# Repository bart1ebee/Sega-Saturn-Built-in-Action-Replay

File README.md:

# Sega-Saturn-Built-in-Action-Replay

This will allow you to take an action replay for a Sega Saturn and solder it to the under side of the cart connector to bypass a bad slot.

This currently is setup to work with VA 0 and .5 motherboards I believe it will work with VA1 but do not have a system to test with. In the future I'd like to make the same board or possibly a few boards for all revisions.

## Features

- Enable / Disable with a switch
- Swap between Action Replay and [Pseudo Saturn Kai](https://ppcenter.webou.net/pskai/)
- If PAL equations can be extracted this could be buildable without buying an action replay 

## Parts Needed

- PCB
- Action Replay containing the following
    - 2x HM5117800J
    - 2x sst29ee020-120-4c-nh
    - 2x 74157
    - PAL16L8 
    - PAL24
- Soldering skills
- Optional: the STL folder has a fake cart slot with catches to hold the Action Replay Cart that I added switches to.

## Building

1. Order Boards from a PCB supplier
2. Disassemble an Action replay and assemble on new board
3. SW1 is a SPDT On-On switch and SW2 is a SPST switch On-Off
4. Solder to underside of card slot

## Help Wanted

 Anyone that can extract the logic equations from the PAL Chips.

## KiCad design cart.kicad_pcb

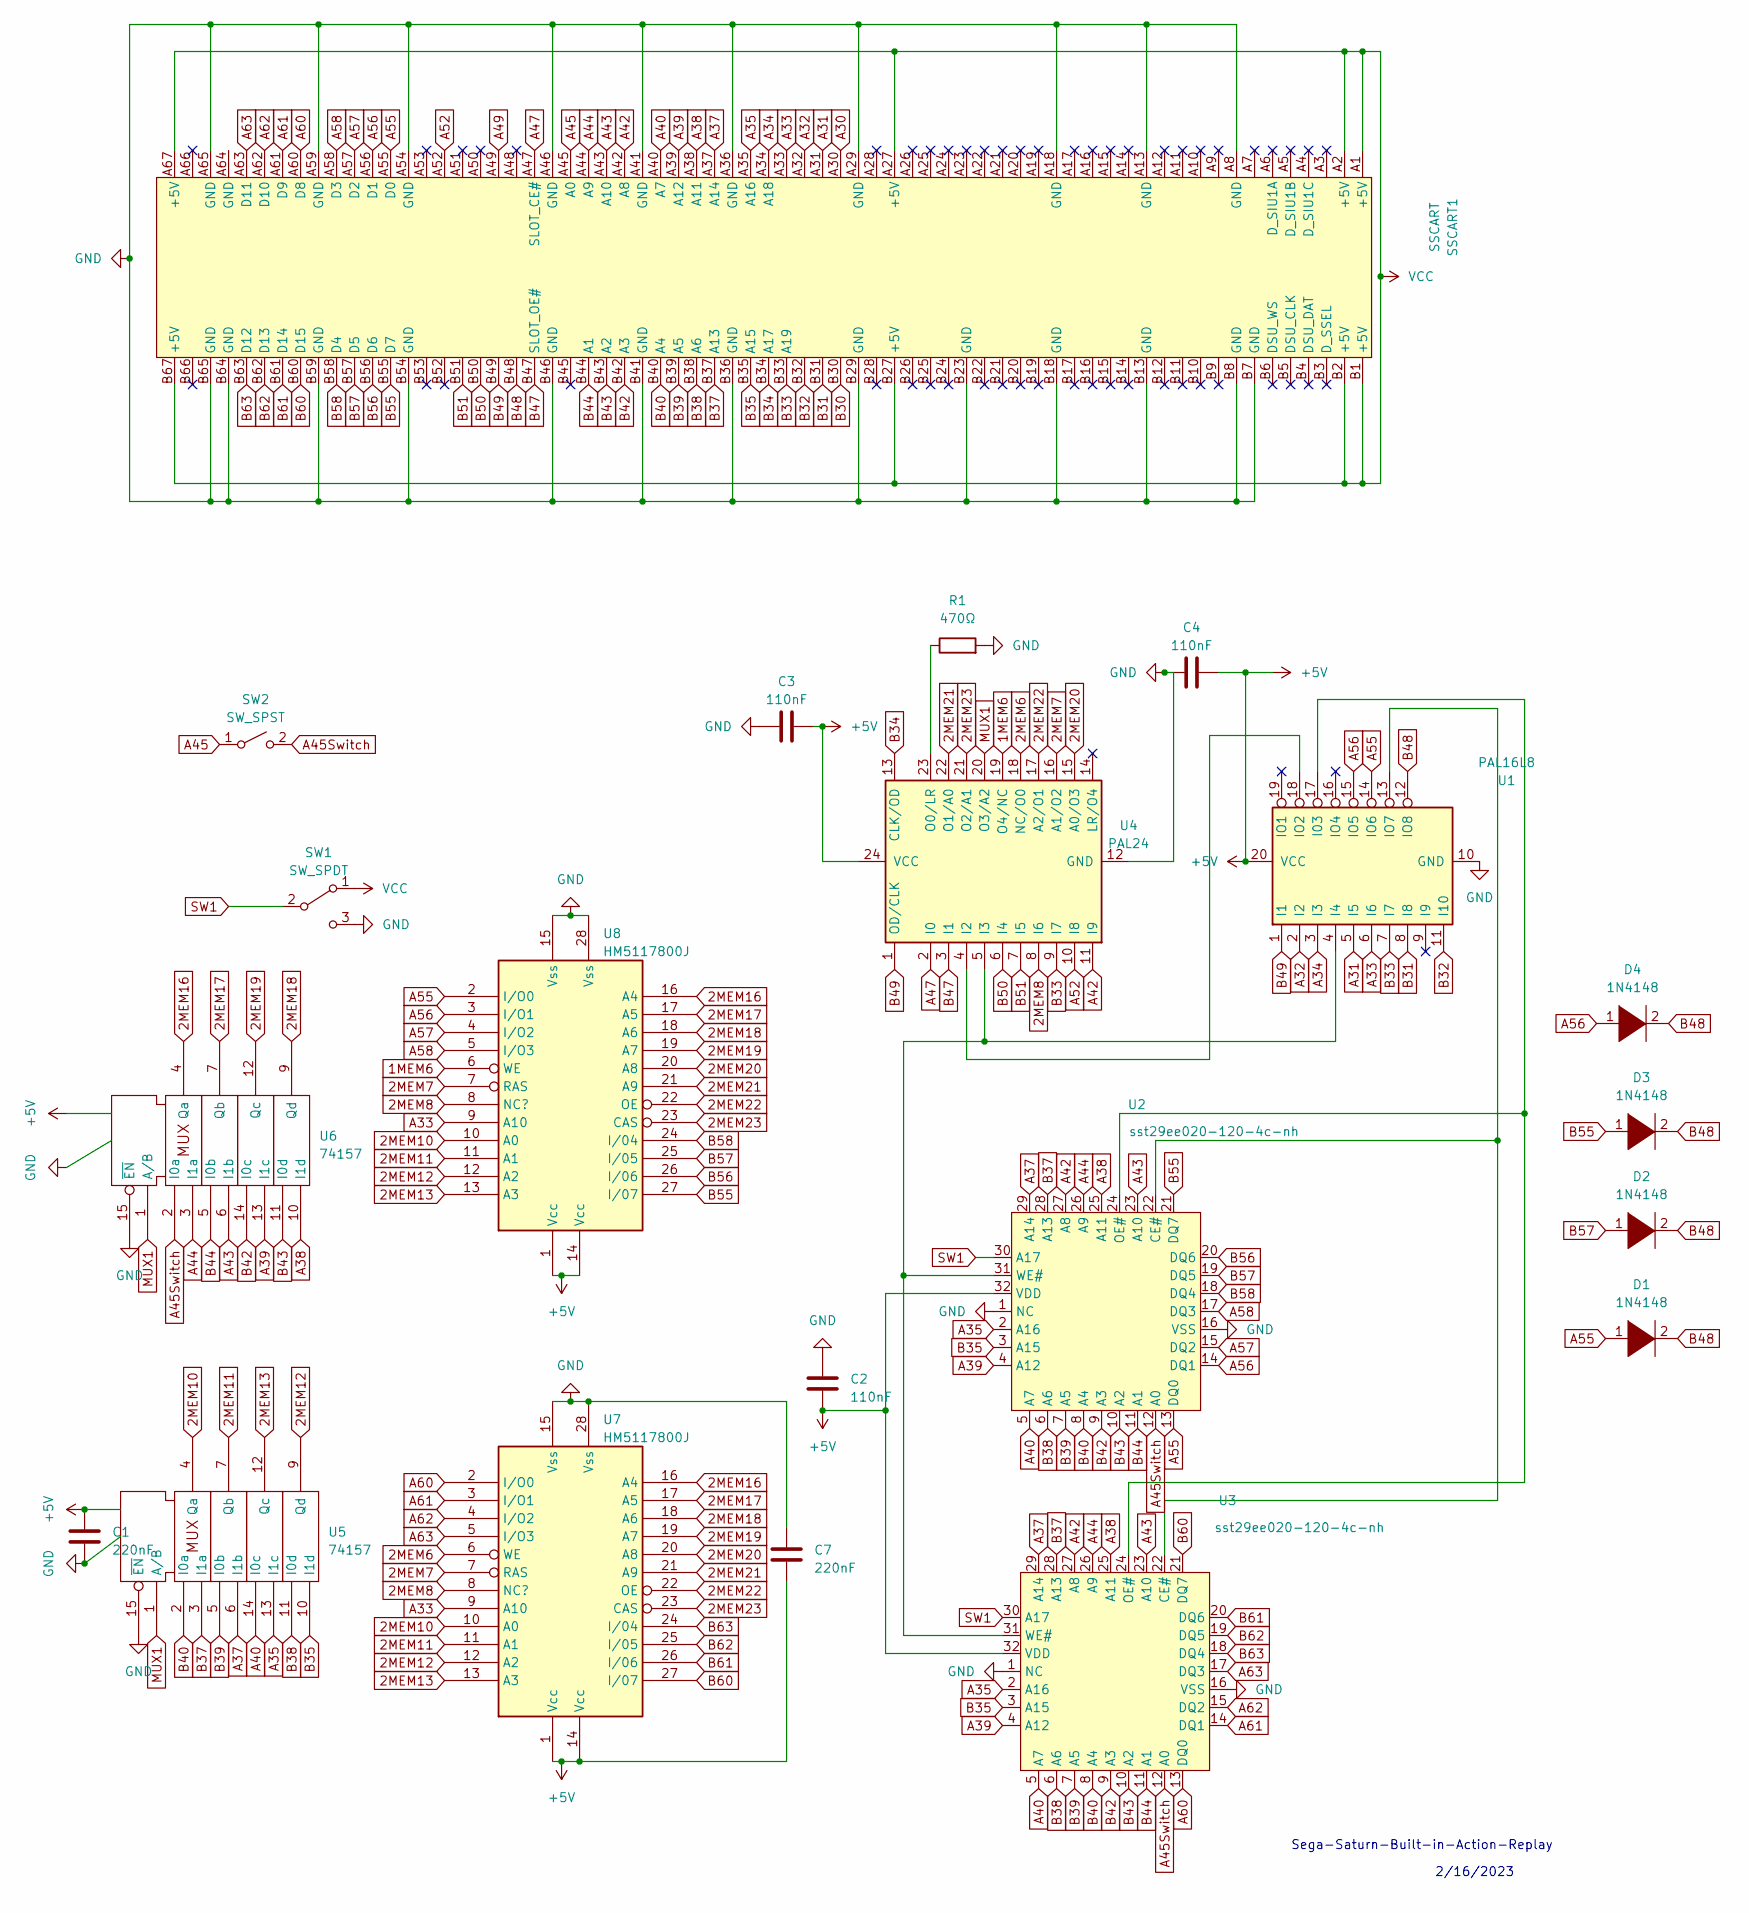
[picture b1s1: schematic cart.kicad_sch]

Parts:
C1, C7: 220nF; C_0805_2012Metric_Pad1.18x1.45mm_HandSolder
C2, C3, C4: 110nF; C_0805_2012Metric_Pad1.18x1.45mm_HandSolder
D1, D2, D3, D4: 1N4148; D_MiniMELF_Handsoldering
R1: 470Ω; R_0805_2012Metric_Pad1.20x1.40mm_HandSolder
SSCART1: SSCART; Sega Cart
SW1: SW_SPDT; JST_XH_S3B-XH-A-1_1x03_P2.50mm_Horizontal
SW2: SW_SPST; JST_XH_S2B-XH-A_1x02_P2.50mm_Horizontal
U1: PAL16L8; DIP-20_W7.62mm_Socket
U2, U3: sst29ee020-120-4c-nh; PLCC-32_11.4x14.0mm_P1.27mm
U4: PAL24; DIP-24_W7.62mm_Socket
U5, U6: 74157; DIP-16_W7.62mm_Socket
U7, U8: HM5117800J; SOIC-28

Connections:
1MEM6: U4.19 (O4/NC), U8.6 (WE)
2MEM6: U4.18 (NC/O0), U7.6 (WE)
2MEM7: U4.16 (A1/O2), U7.7 (RAS), U8.7 (RAS)
2MEM8: U4.8 (I6), U7.8 (NC?), U8.8 (NC?)
2MEM10: U5.4 (Qa), U7.10 (A0), U8.10 (A0)
2MEM11: U5.7 (Qb), U7.11 (A1), U8.11 (A1)
2MEM12: U5.9 (Qd), U7.12 (A2), U8.12 (A2)
2MEM13: U5.12 (Qc), U7.13 (A3), U8.13 (A3)
2MEM16: U6.4 (Qa), U7.16 (A4), U8.16 (A4)
2MEM17: U6.7 (Qb), U7.17 (A5), U8.17 (A5)
2MEM18: U6.9 (Qd), U7.18 (A6), U8.18 (A6)
2MEM19: U6.12 (Qc), U7.19 (A7), U8.19 (A7)
2MEM20: U4.15 (A0/O3), U7.20 (A8), U8.20 (A8)
2MEM21: U4.22 (O1/A0), U7.21 (A9), U8.21 (A9)
2MEM22: U4.17 (A2/O1), U7.22 (OE), U8.22 (OE)
2MEM23: U4.21 (O2/A1), U7.23 (CAS), U8.23 (CAS)
A30: SSCART1.A30
A31: SSCART1.A31, U1.5 (I5)
A32: SSCART1.A32, U1.2 (I2)
A33: SSCART1.A33, U1.6 (I6), U7.9 (A10), U8.9 (A10)
A34: SSCART1.A34 (A18), U1.3 (I3)
A35: SSCART1.A35 (A16), U2.2 (A16), U3.2 (A16), U5.13 (I1c)
A37: SSCART1.A37 (A14), U2.29 (A14), U3.29 (A14), U5.6 (I1b)
A38: SSCART1.A38 (A11), U2.25 (A11), U3.25 (A11), U6.10 (I1d)
A39: SSCART1.A39 (A12), U2.4 (A12), U3.4 (A12), U6.13 (I1c)
A40: SSCART1.A40 (A7), U2.5 (A7), U3.5 (A7), U5.14 (I0c)
A42: SSCART1.A42 (A8), U2.27 (A8), U3.27 (A8), U4.11 (I9)
A43: SSCART1.A43 (A10), U2.23 (A10), U3.23 (A10), U6.6 (I1b)
A44: SSCART1.A44 (A9), U2.26 (A9), U3.26 (A9), U6.3 (I1a)
A45: SSCART1.A45 (A0), SW2.1 (A)
A45Switch: SW2.2 (B), U2.12 (A0), U3.12 (A0), U6.2 (I0a)
A47: SSCART1.A47 (SLOT_CE#), U4.2 (I0)
A49: SSCART1.A49
A52: SSCART1.A52, U4.10 (I8)
A55: D1.1 (K), SSCART1.A55 (D0), U1.14 (IO6), U2.13 (DQ0), U8.2 (I/O0)
A56: D4.1 (K), SSCART1.A56 (D1), U1.15 (IO5), U2.14 (DQ1), U8.3 (I/O1)
A57: SSCART1.A57 (D2), U2.15 (DQ2), U8.4 (I/O2)
A58: SSCART1.A58 (D3), U2.17 (DQ3), U8.5 (I/O3)
A60: SSCART1.A60 (D8), U3.13 (DQ0), U7.2 (I/O0)
A61: SSCART1.A61 (D9), U3.14 (DQ1), U7.3 (I/O1)
A62: SSCART1.A62 (D10), U3.15 (DQ2), U7.4 (I/O2)
A63: SSCART1.A63 (D11), U3.17 (DQ3), U7.5 (I/O3)
B30: SSCART1.B30
B31: SSCART1.B31, U1.8 (I8)
B32: SSCART1.B32, U1.11 (I10)
B33: SSCART1.B33 (A19), U1.7 (I7), U4.9 (I7)
B34: SSCART1.B34 (A17), U4.13 (CLK/OD)
B35: SSCART1.B35 (A15), U2.3 (A15), U3.3 (A15), U5.10 (I1d)
B37: SSCART1.B37 (A13), U2.28 (A13), U3.28 (A13), U5.3 (I1a)
B38: SSCART1.B38 (A6), U2.6 (A6), U3.6 (A6), U5.11 (I0d)
B39: SSCART1.B39 (A5), U2.7 (A5), U3.7 (A5), U5.5 (I0b)
B40: SSCART1.B40 (A4), U2.8 (A4), U3.8 (A4), U5.2 (I0a)
B42: SSCART1.B42 (A3), U2.9 (A3), U3.9 (A3), U6.14 (I0c)
B43: SSCART1.B43 (A2), U2.10 (A2), U3.10 (A2), U6.11 (I0d)
B44: SSCART1.B44 (A1), U2.11 (A1), U3.11 (A1), U6.5 (I0b)
B47: SSCART1.B47 (SLOT_OE#), U4.3 (I1)
B48: D1.2 (A), D2.2 (A), D3.2 (A), D4.2 (A), SSCART1.B48, U1.12 (IO8)
B49: SSCART1.B49, U1.1 (I1), U4.1 (OD/CLK)
B50: SSCART1.B50, U4.6 (I4)
B51: SSCART1.B51, U4.7 (I5)
B55: D3.1 (K), SSCART1.B55 (D7), U2.21 (DQ7), U8.27 (I/07)
B56: SSCART1.B56 (D6), U2.20 (DQ6), U8.26 (I/06)
B57: D2.1 (K), SSCART1.B57 (D5), U2.19 (DQ5), U8.25 (I/05)
B58: SSCART1.B58 (D4), U2.18 (DQ4), U8.24 (I/04)
B60: SSCART1.B60 (D15), U3.21 (DQ7), U7.27 (I/07)
B61: SSCART1.B61 (D14), U3.20 (DQ6), U7.26 (I/06)
B62: SSCART1.B62 (D13), U3.19 (DQ5), U7.25 (I/05)
B63: SSCART1.B63 (D12), U3.18 (DQ4), U7.24 (I/04)
GND: C1.2, C2.1, C3.2, C4.1, C7.1, R1.2, SSCART1.A8 (GND), SSCART1.A13 (GND), SSCART1.A18 (GND), SSCART1.A29 (GND), SSCART1.A36 (GND), SSCART1.A41 (GND), SSCART1.A46 (GND), SSCART1.A54 (GND), SSCART1.A59 (GND), SSCART1.A65 (GND), SSCART1.B7 (GND), SSCART1.B8 (GND), SSCART1.B13 (GND), SSCART1.B18 (GND), SSCART1.B23 (GND), SSCART1.B29 (GND), SSCART1.B36 (GND), SSCART1.B41 (GND), SSCART1.B46 (GND), SSCART1.B54 (GND), SSCART1.B59 (GND), SSCART1.B64 (GND), SSCART1.B65 (GND), SW1.3 (C), U1.10 (GND), U2.1 (NC), U2.16 (VSS), U3.1 (NC), U3.16 (VSS), U4.12 (GND), U5.8 (GND), U5.15 (~EN), U6.8 (GND), U6.15 (~EN), U7.15 (Vss), U7.28 (Vss), U8.15 (Vss), U8.28 (Vss)
MUX1: U4.20 (O3/A2), U5.1 (A/B), U6.1 (A/B)
unnamed: U1.17 (I03), U2.24 (OE#), U3.24 (OE#)
unnamed: U1.4 (I4), U2.31 (WE#), U3.31 (WE#), U4.5 (I3)
unnamed: U1.18 (IO2), U4.4 (I2)
unnamed: U1.13 (IO7), U2.22 (CE#), U3.22 (CE#)
unnamed: R1.1, U4.23 (O0/LR)
SW1: SW1.2 (B), U2.30 (A17), U3.30 (A17)

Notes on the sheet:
Sega-Saturn-Built-in-Action-Replay
2/16/2023

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
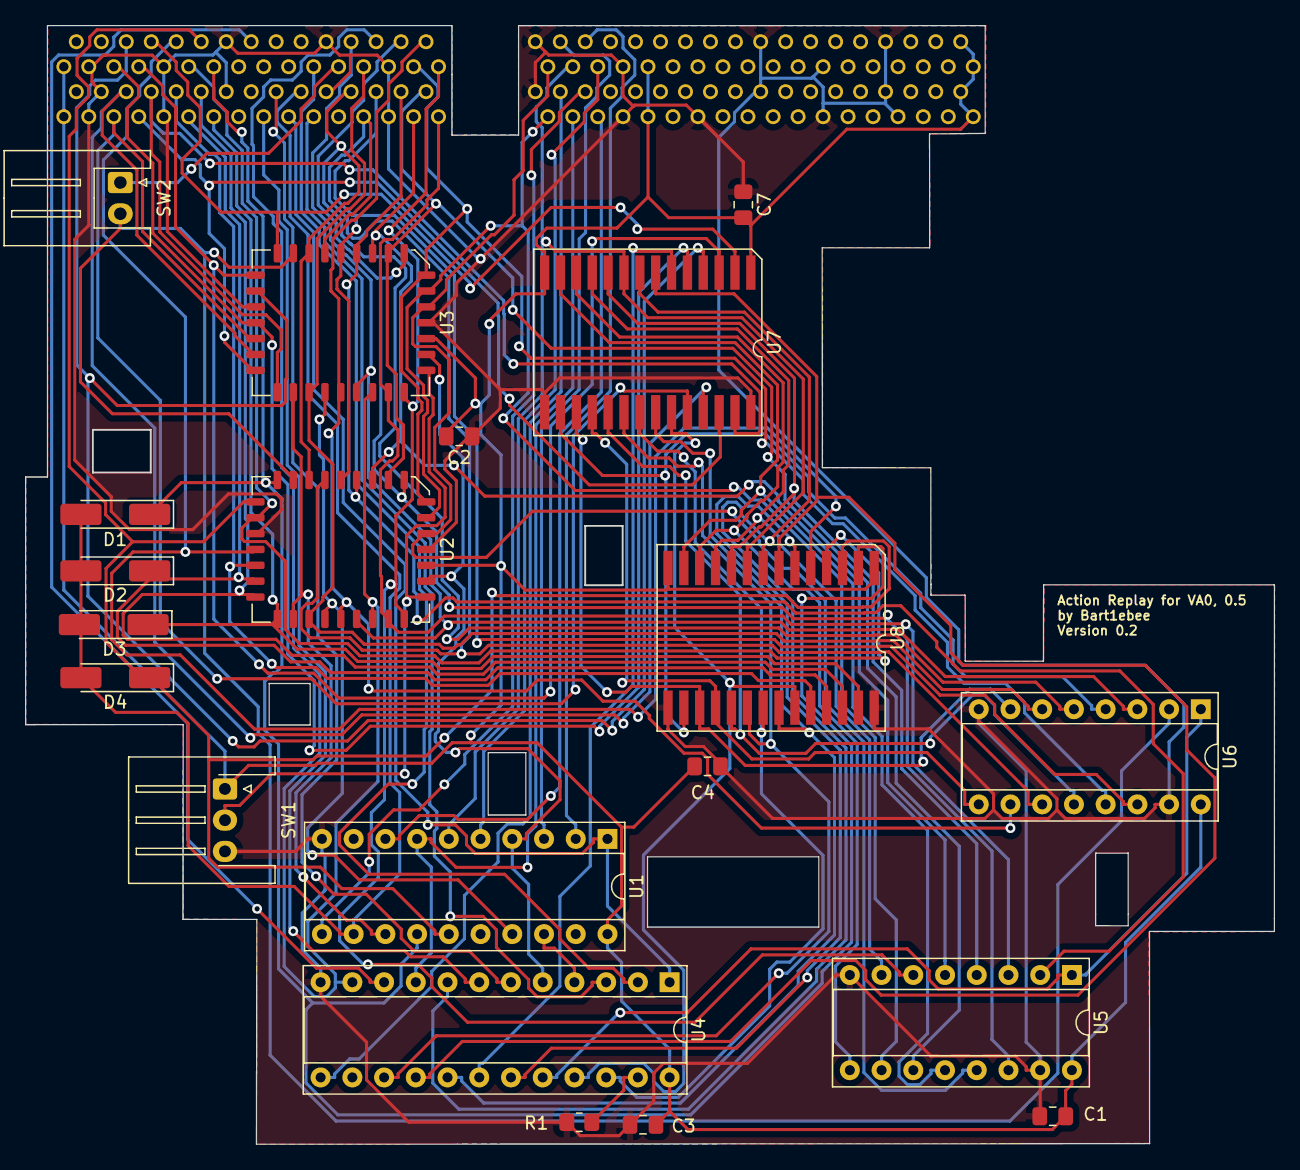
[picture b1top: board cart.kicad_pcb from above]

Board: 2 copper layers, 100.0 x 89.6 mm, 21 parts (0 on the bottom side), 74 nets.

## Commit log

2023-02-17 Update to Readme
    Updated Readme spelling mistakes and little more information. Also updated library link for sst29ee020 and HM5117800J
2023-02-17 More updates
    More updates to the readme (should not make updates in the middle of the night). Added Some photos.
2023-02-17 More Readme updates
    More Readme updates
